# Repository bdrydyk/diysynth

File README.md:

# diysynth
Diy Synth with reference to published designs

This repository contains reference designs for synth projects as well as works in progress code and eagle data.

## Reference Designs

### Midi to CV

* [ATMega Midi to CV](https://github.com/jbeuckm/atmega_midi_cv_monosynth)
* [Teensy midi to CV 1](https://github.com/elkayem/usbMIDI2CV_MC)
* [Teensy midi to CV 2](http://www.marc-nostromo.com/midi-control-for-the-monotron-using-a-teensy-3-0/)
* [midi to CV basics](http://www.kentonuk.com/info/midi-cv-info.shtml)
* [Midi2CV Mk2](https://midisizer.com/midi2cv-mk2/)

### VCO

* [Thomas Henry’s VCO MAXIMUS](http://www.synthdiy.fonitronik.de/PDF/TH-VCO-MAXIMUS-doc-v1.pdf)
* [modular addict - NLC CEM3340 VCO PCB](https://modularaddict.com/parts/pcbs/nlc-cem3340-pcb)
* [muff wiggler - CEM3340 VCO](https://www.muffwiggler.com/forum/viewtopic.php?t=170054&highlight=)
* [same as above](https://www.dsl-man.de/display/CHECKMATE/CEM3340+VCO)
* [MFOS - Modular VCO](http://musicfromouterspace.com/analogsynth_new/VCO20120618REV0/VCO20120618REV0.html)
* [MFOS - Sound Lab Mini-Synth Mark II](http://musicfromouterspace.com/analogsynth_new/SOUNDLABMINIMARKII/page1.php)
* [birthofasynth - CEM3340 based VCO](http://www.birthofasynth.com/Thomas_Henry/Pages/VCO_Maximus-Detail.html#VCO%20Maximus)
* [sruthi - VCO](https://mutable-instruments.net/archive/shruthi/build/)
* [another CEM3340 VCO with an example PCB](https://modularaddict.com/nlc-cem3340-pcb)

### VCF

### ADSR

### VCA

### Other

* [Modular PCBs](https://modularaddict.com/parts/pcbs)
* [the vco](http://secretlifeofsynthesizers.com/the-vco/)
* [thonk music thing](https://www.thonk.co.uk/shop/music-thing-modular-simple-eq-full-kit/)

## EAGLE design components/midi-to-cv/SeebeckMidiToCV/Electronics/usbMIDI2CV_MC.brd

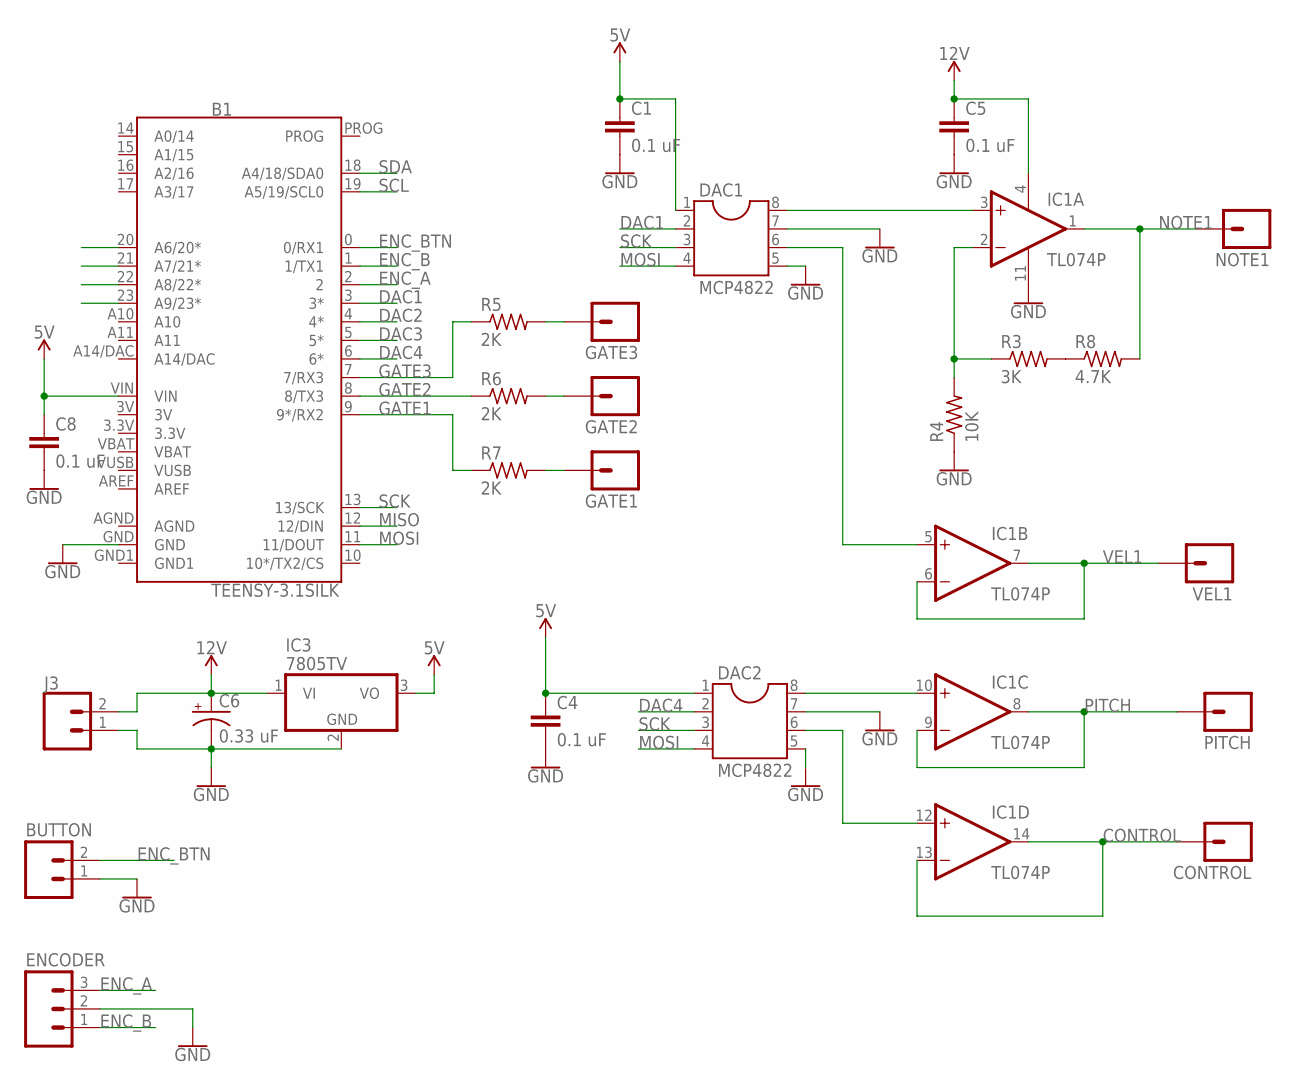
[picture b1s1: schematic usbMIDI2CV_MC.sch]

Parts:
B1: TEENSY-3.1SILK; TEENSY-3.1
BUTTON: M02LOCK_LONGPADS; 1X02_LOCK_LONGPADS
C1, C4, C5, C8: 0.1 uF; CAP-PTH-SMALL
C6: 0.33 uF; CPOL-RADIAL-100UF-25V
CONTROL: M01PTH_NO_SILK_YES_STOP; 1X01_NO_SILK
DAC1, DAC2: MCP4822; SOCKET-08
ENCODER: M03LONGPADS; 1X03_LONGPADS
GATE1, GATE2, GATE3: M01PTH_NO_SILK_YES_STOP; 1X01_NO_SILK
IC1: TL074P; DIL14
IC3: 7805TV; TO220V
J3: CONN_025MM; SCREWTERMINAL-5MM-2
NOTE1: M01PTH_NO_SILK_YES_STOP; 1X01_NO_SILK
PITCH: M01PTH_NO_SILK_YES_STOP; 1X01_NO_SILK
R3: 3K; 0207/10
R4: 10K; 0207/10
R5, R6, R7: 2K; 0207/10
R8: 4.7K; 0207/10
VEL1: M01PTH_NO_SILK_YES_STOP; 1X01_NO_SILK

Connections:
3.3V: B1.3.3V
3V: B1.3V
5V: B1.VIN, C1.1, C4.1, C8.1, DAC1.1, DAC2.1, IC3.3 (VO)
12V: C5.1, C6.1 (+), IC1.4 (V+), IC3.1 (VI), J3.2
AGND: B1.AGND
CONTROL: CONTROL.1, IC1.13 (-IN), IC1.14 (OUT)
DAC1: B1.3 (3*), DAC1.2
DAC2: B1.4 (4*)
DAC3: B1.5 (5*)
DAC4: B1.6 (6*), DAC2.2
ENC_A: B1.2, ENCODER.3
ENC_B: B1.1 (1/TX1), ENCODER.1
ENC_BTN: B1.0 (0/RX1), BUTTON.2
GATE1: B1.9 (9*/RX2), R7.1
GATE2: B1.8 (8/TX3), R6.1
GATE3: B1.7 (7/RX3), R5.1
GND: B1.GND, BUTTON.1, C1.2, C4.2, C5.2, C6.2 (-), C8.2, DAC1.5, DAC1.7, DAC2.5, DAC2.7, ENCODER.2, IC1.11 (V-), IC3.2 (GND), J3.1, R4.1
GND1: B1.GND1
MISO: B1.12 (12/DIN)
MOSI: B1.11 (11/DOUT), DAC1.4, DAC2.4
unnamed: DAC1.8, IC1.3 (+IN)
unnamed: R3.2, R8.1
unnamed: IC1.2 (-IN), R3.1, R4.2
unnamed: DAC1.6, IC1.5 (+IN)
unnamed: DAC2.6, IC1.12 (+IN)
unnamed: DAC2.8, IC1.10 (+IN)
unnamed: GATE3.1, R5.2
unnamed: GATE2.1, R6.2
unnamed: GATE1.1, R7.2
NOTE1: IC1.1 (OUT), NOTE1.1, R8.2
PITCH: IC1.8 (OUT), IC1.9 (-IN), PITCH.1
SCK: B1.13 (13/SCK), DAC1.3, DAC2.3
SCL: B1.19 (A5/19/SCL0)
SDA: B1.18 (A4/18/SDA0)
VBAT: B1.VBAT
VEL1: IC1.6 (-IN), IC1.7 (OUT), VEL1.1
VUSB: B1.VUSB

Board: 2 copper layers, 26 parts (0 on the bottom side), 26 nets, no tracks yet.

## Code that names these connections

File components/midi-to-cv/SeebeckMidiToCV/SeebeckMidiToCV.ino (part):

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#define GATE_CH1  3
#define GATE_CH2  4

#define ENC_A   14
#define ENC_B   15
#define ENC_BTN 16


#define GATE(CH) (CH==0 ? GATE_CH0 : (CH==1 ? GATE_CH1 : GATE_CH2))
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 pinMode(DAC2, OUTPUT);
 pinMode(DAC3, OUTPUT);
 pinMode(DAC4, OUTPUT);
 pinMode(ENC_A, INPUT_PULLUP);
 pinMode(ENC_B, INPUT_PULLUP);
 pinMode(ENC_BTN,INPUT_PULLUP);
  
 digitalWrite(GATE_CH0,LOW);
 digitalWrite(GATE_CH1,LOW);
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}

// setVoltage -- Set DAC voltage output
// dacpin: chip select pin for DAC.  Note and velocity on DAC1, pitch bend and CC on DAC2
// channel: 0 (A) or 1 (B).  
// gain: 0 = 1X, 1 = 2X.  
// mV: integer 0 to 4095.  If gain is 1X, mV is in units of half mV (i.e., 0 to 2048 mV).
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
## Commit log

2018-04-12 init
2018-04-12 added readme

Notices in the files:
components/midi-to-cv/SeebeckMidiToCV/SeebeckMidiToCV.ino:
Copyright (C) 2018  Larry McGovern
This program is free software: you can redistribute it and/or modify
it under the terms of the GNU General Public License as published by
the Free Software Foundation, either version 3 of the License, or
(at your option) any later version.
parts and their libraries:
SparkFun-Connectors: Licensing: Creative Commons ShareAlike 4.0 International - https://creativecommons.org/licenses/by-sa/4.0
